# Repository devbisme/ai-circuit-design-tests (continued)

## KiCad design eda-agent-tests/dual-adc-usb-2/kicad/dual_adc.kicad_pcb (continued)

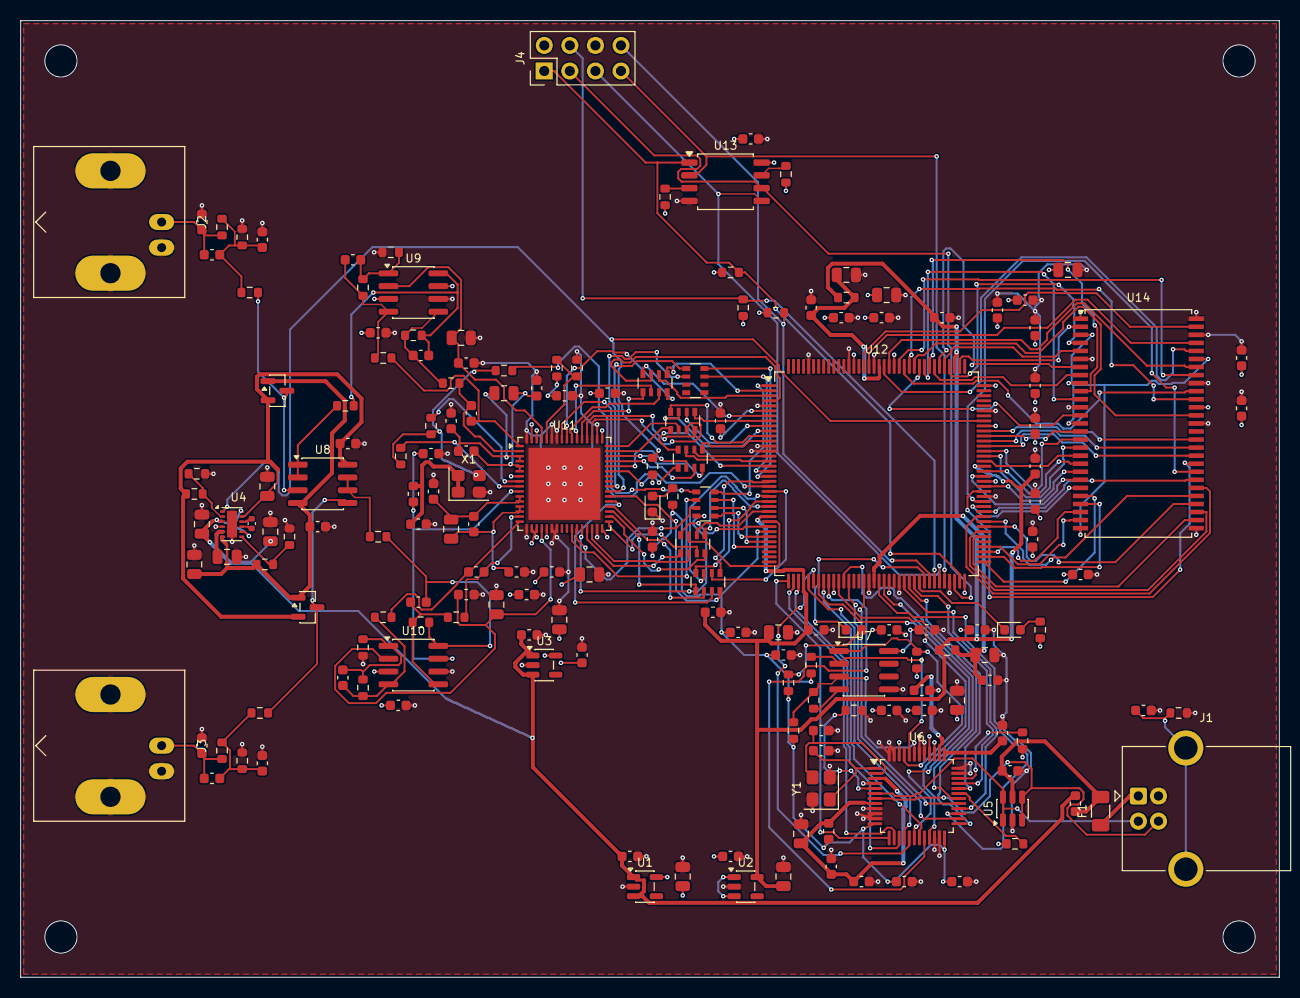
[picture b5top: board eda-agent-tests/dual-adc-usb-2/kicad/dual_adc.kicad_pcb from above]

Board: 4 copper layers, 125.0 x 95.0 mm, 179 parts (0 on the bottom side), 185 nets.

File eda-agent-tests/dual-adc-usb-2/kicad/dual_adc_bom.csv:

"Refs","Value","Footprint","MPN","Manufacturer","Tolerance","Qty"
"C1,C11,C18,C25","4.7uF","Capacitor_SMD:C_0805_2012Metric","","","","4"
"C2,C4,C6,C7,C49,C50,C54,C55","1uF","Capacitor_SMD:C_0603_1608Metric","","","","8"
"C3,C5,C8,C61,C69,C80,C81,C83,C93","10uF","Capacitor_SMD:C_0805_2012Metric","","","","9"
"C9,C12,C13,C48,C51,C53,C56","2.2uF","Capacitor_SMD:C_0805_2012Metric","","","","7"
"C10","1uF","Capacitor_SMD:C_0402_1005Metric","","","","1"
"C14","4.7nF","Capacitor_SMD:C_0603_1608Metric","","","","1"
"C15,C19-C24,C26-C30,C36,C37,C44,C45,C47,C52,C57-C60,C62-C68,C70-C79,C82,C84-C92","100nF","Capacitor_SMD:C_0603_1608Metric","","","","49"
"C16,C17","27pF","Capacitor_SMD:C_0603_1608Metric","","","","2"
"C31,C39","12pF","Capacitor_SMD:C_0603_1608Metric","","","","2"
"C32,C40","2.7pF","Capacitor_SMD:C_0603_1608Metric","","","","2"
"C33,C41","22pF","Capacitor_SMD:C_0603_1608Metric","","","","2"
"C34,C35,C42,C43","33pF","Capacitor_SMD:C_0603_1608Metric","","","","4"
"C38,C46","100pF","Capacitor_SMD:C_0603_1608Metric","","","","2"
"D1","Green","LED_SMD:LED_0603_1608Metric","","","","1"
"D2,D3","BAV99","Package_TO_SOT_SMD:SOT-23","BAV99,215","Nexperia","","2"
"D4,D5","Yellow","LED_SMD:LED_0603_1608Metric","","","","2"
"F1","750mA","Fuse:Fuse_1206_3216Metric","0ZCJ0050AF2E","Bel Fuse","","1"
"FB1","120R@100MHz 2A","Inductor_SMD:L_0603_1608Metric","BLM18AG601SN1D","Murata","","1"
"FB2,FB3","600R@100MHz","Inductor_SMD:L_0603_1608Metric","BLM18AG601SN1D","Murata","","2"
"J1","USB_B","Connector_USB:USB_B_OST_USB-B1HSxx_Horizontal","USB-B1HSW6","On Shore Technology","","1"
"J2","BNC_A","Connector_Coaxial:BNC_Amphenol_B6252HB-NPP3G-50_Horizontal","B6252HB-NPP3G-50","Amphenol RF","","1"
"J3","BNC_B","Connector_Coaxial:BNC_Amphenol_B6252HB-NPP3G-50_Horizontal","B6252HB-NPP3G-50","Amphenol RF","","1"
"J4","PROG","Connector_PinHeader_2.54mm:PinHeader_2x04_P2.54mm_Vertical","","","","1"
"R1,R9,R10,R12-R14,R33,R40-R44","10k","Resistor_SMD:R_0603_1608Metric","","","","12"
"R2","232k","Resistor_SMD:R_0603_1608Metric","","","","1"
"R3,R5","100k","Resistor_SMD:R_0603_1608Metric","","","","2"
"R4","226k","Resistor_SMD:R_0603_1608Metric","","","","1"
"R6,R17-R21,R26-R30,R45,R46","1k","Resistor_SMD:R_0603_1608Metric","","","","13"
"R7","1M","Resistor_SMD:R_0603_1608Metric","","","","1"
"R8","12k","Resistor_SMD:R_0603_1608Metric","","","1%","1"
"R11","2.2k","Resistor_SMD:R_0603_1608Metric","","","","1"
"R15,R24","909k","Resistor_SMD:R_0603_1608Metric","","","0.1%","2"
"R16,R25","90.9k","Resistor_SMD:R_0603_1608Metric","","","0.1%","2"
"R22,R23,R31,R32","49.9","Resistor_SMD:R_0603_1608Metric","","","","4"
"R34","20k","Resistor_SMD:R_0603_1608Metric","","","","1"
"R35-R37","33","Resistor_SMD:R_0603_1608Metric","","","","3"
"R38,R39","100","Resistor_SMD:R_0603_1608Metric","","","","2"
"RN1-RN7","33","Resistor_SMD:R_Array_Convex_4x0603","CAY16-330J4LF","Bourns","","7"
"U1","AP2112K-3.3","Package_TO_SOT_SMD:SOT-23-5","AP2112K-3.3TRG1","Diodes Inc","","1"
"U2","AP2112K-1.2","Package_TO_SOT_SMD:SOT-23-5","AP2112K-1.2TRG1","Diodes Inc","","1"
"U3","LP5907MFX-3.3","Package_TO_SOT_SMD:SOT-23-5","LP5907MFX-3.3/NOPB","Texas Instruments","","1"
"U4","LM27762","Package_SON:WSON-12-1EP_3x2mm_P0.5mm_EP1x2.65","LM27762DSSR","Texas Instruments","","1"
"U5","USBLC6-2SC6","Package_TO_SOT_SMD:SOT-23-6","USBLC6-2SC6","STMicroelectronics","","1"
"U6","FT232HL","Package_QFP:LQFP-48_7x7mm_P0.5mm","FT232HL-REEL","FTDI","","1"
"U7","93LC56B","Package_SO:SOIC-8_3.9x4.9mm_P1.27mm","93LC56BT-I/SN","Microchip","","1"
"U8","OPA1656ID","Package_SO:SOIC-8_3.9x4.9mm_P1.27mm","OPA1656IDR","Texas Instruments","","1"
"U9,U10","THS4521ID","Package_SO:SOIC-8_3.9x4.9mm_P1.27mm","THS4521IDR","Texas Instruments","","2"
"U11","LTC2290CUP","Package_DFN_QFN:QFN-64-1EP_9x9mm_P0.5mm_EP7.15x7.15mm","LTC2290CUP#PBF","Analog Devices","","1"
"U12","ICE40HX4K-TQ144","Package_QFP:TQFP-144_20x20mm_P0.5mm","ICE40HX4K-TQ144","Lattice","","1"
"U13","W25Q32JVSS","Package_SO:SOIC-8_5.3x5.3mm_P1.27mm","W25Q32JVSSIQ","Winbond","","1"
"U14","MT48LC16M16A2TG-6A","Package_SO:TSOP-II-54_22.2x10.16mm_P0.8mm","MT48LC16M16A2P-6A:G","Micron","","1"
"X1","ASE-10.000MHz","Oscillator:Oscillator_SMD_Abracon_ASE-4Pin_3.2x2.5mm","ASE-10.000MHZ-LC-T","Abracon","","1"
"Y1","12MHz","Crystal:Crystal_SMD_3225-4Pin_3.2x2.5mm","ABM8-12.000MHZ-B2-T","Abracon","","1"

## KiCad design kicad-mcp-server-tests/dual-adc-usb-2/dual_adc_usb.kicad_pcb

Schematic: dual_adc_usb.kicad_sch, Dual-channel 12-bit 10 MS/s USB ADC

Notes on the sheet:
Power: USB-C input, regulators
Analog front ends (A, B)
ADC and sample clock
FPGA, SDRAM, config flash
USB 2.0 interface (FT2232H)
DUAL-CHANNEL 12-BIT 10 MS/s USB ADC (see DESIGN.md for options and rationale) Signal path (per channel): BNC -> 1 Mohm || ~19 pF input, compensated /10.06 divider (2 x 453k + 100k) -> BAV99 clamp to +/-3.3 V -> OPA810 FET-input unity buffer -> THS4521 FDA (G = 1, VOCM = ADC VCM 1.5 V) -> 49.9R/33pF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

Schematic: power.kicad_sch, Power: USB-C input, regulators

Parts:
C1: 4.7nF 100V; C_0603_1608Metric
C2: 4.7uF; C_0805_2012Metric
C3: 22uF; C_0805_2012Metric
C4: 100nF; C_0603_1608Metric
C5, C6, C7, C8, C9, C10, C11: 1uF; C_0603_1608Metric
C12, C13: 2.2uF; C_0603_1608Metric
D1: green; LED_0603_1608Metric
F1: 0.75A hold; Fuse_1206_3216Metric
H1, H2, H3, H4: M3; MountingHole_3.2mm_M3
J1: USB-C (USB 2.0); USB_C_Receptacle_GCT_USB4105-xx-A_16P_TopMnt_Horizontal
L1: 2.2uH 1.5A; L_Taiyo-Yuden_NR-30xx
R1, R2: 5.1k; R_0603_1608Metric
R3: 1M; R_0603_1608Metric
R4: 169k 1%; R_0603_1608Metric
R5: 100k 1%; R_0603_1608Metric
R6: 1k; R_0603_1608Metric
U1: USBLC6-2SC6; SOT-23-6
U2: TPS62162DSGR; WSON-8-1EP_2x2mm_P0.5mm_EP0.9x1.6mm_ThermalVias
U3: AP2112K-1.2; SOT-23-5
U4: LP5907MFX-3.3; SOT-23-5
U5: LP5907MFX-3.0; SOT-23-5
U6: LM27761DSGR; WSON-8-1EP_2x2mm_P0.5mm_EP0.9x1.6mm

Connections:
+1V2: C6.1, U3.5 (VOUT); also elsewhere on the board
+3V0A: C10.1, U5.5 (OUT); also elsewhere on the board
+3V3: C3.1, C4.1, C5.1, L1.2, R6.1, U2.6 (VOS), U3.1 (VIN), U3.3 (EN); also elsewhere on the board
+3V3A: C8.1, U4.5 (OUT); also elsewhere on the board
+5V: C2.1, C7.1, C9.1, F1.2, U2.2 (VIN), U2.3 (EN), U4.1 (IN), U4.3 (EN), U5.1 (IN), U5.3 (EN), U6.1 (VIN), U6.6 (EN)
-3V3A: C13.1, R4.1, U6.4 (VOUT); also elsewhere on the board
CC1: J1.A5 (CC1), R1.1
CC2: J1.B5 (CC2), R2.1
CPOUT: C12.1, U6.3 (CPOUT)
CP_N: C11.2, U6.7 (C-)
CP_P: C11.1, U6.8 (C+)
GND: C1.2, C2.2, C3.2, C4.2, C5.2, C6.2, C7.2, C8.2, C9.2, C10.2, C12.2, C13.2, D1.1 (K), J1.A1 (GND), J1.A12 (GND), J1.B1 (GND), J1.B12 (GND), R1.2, R2.2, R3.2, R5.2, U1.2 (GND), U2.1 (PGND), U2.4 (AGND), U2.5 (FB), U2.9 (PAD), U3.2 (GND), U4.2 (GND), U5.2 (GND), U6.2 (GND), U6.9 (PAD); also elsewhere on the board
LED_PWR: D1.2 (A), R6.2
NFB: R4.2, R5.1, U6.5 (VFB)
SHIELD: C1.1, J1.S1 (SHIELD), R3.1
SW_3V3: L1.1, U2.7 (SW)
USB_DM: J1.A7 (D-), J1.B7 (D-), U1.3 (I/O2), U1.4 (I/O2); also elsewhere on the board
USB_DP: J1.A6 (D+), J1.B6 (D+), U1.1 (I/O1), U1.6 (I/O1); also elsewhere on the board
VBUS: F1.1, J1.A4 (VBUS), J1.A9 (VBUS), J1.B4 (VBUS), J1.B9 (VBUS), U1.5 (VBUS)

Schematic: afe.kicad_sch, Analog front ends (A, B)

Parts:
C101, C201: 15pF C0G 100V; C_0805_2012Metric
C102, C202: 4.7pF C0G 100V; C_0805_2012Metric
C103, C203: 30pF C0G; C_0603_1608Metric
C104, C204: 4.5-20pF; C_Trimmer_Murata_TZC3
C105, C106, C110, C205, C206, C210: 100nF; C_0603_1608Metric
C107, C108, C207, C208: 22pF C0G; C_0603_1608Metric
C109, C209: 33pF C0G; C_0603_1608Metric
D101, D201: BAV99; SOT-23
J101: BNC IN_A; BNC_Amphenol_B6252HB-NPP3G-50_Horizontal
J201: BNC IN_B; BNC_Amphenol_B6252HB-NPP3G-50_Horizontal
R101, R102, R201, R202: 453k 0.1%; R_0805_2012Metric
R103, R203: 100k 0.1%; R_0603_1608Metric
R104, R204: 1k; R_0603_1608Metric
R105, R106, R107, R108, R205, R206, R207, R208: 1.00k 0.1%; R_0603_1608Metric
R109, R110, R209, R210: 49.9; R_0603_1608Metric
U101, U201: OPA810IDBVR; SOT-23-5
U102, U202: THS4521IDGK; VSSOP-8_3x3mm_P0.65mm

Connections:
+3V3A: C105.1, C110.1, C205.1, C210.1, D101.2 (A), D201.2 (A), U101.5 (V+), U102.3 (V_{S+}), U102.7 (~PD), U201.5 (V+), U202.3 (V_{S+}), U202.7 (~PD); also elsewhere on the board
-3V3A: C106.1, C206.1, D101.1 (K), D201.1 (K), U101.2 (V-), U201.2 (V-); also elsewhere on the board
AIN_N_A: C109.2, R110.2; also elsewhere on the board
AIN_N_B: C209.2, R210.2; also elsewhere on the board
AIN_P_A: C109.1, R109.2; also elsewhere on the board
AIN_P_B: C209.1, R209.2; also elsewhere on the board
ATT_A: C102.2, C103.1, C104.1, D101.3 (K), R102.2, R103.1, R104.1
ATT_B: C202.2, C203.1, C204.1, D201.3 (K), R202.2, R203.1, R204.1
ATT_M_A: R101.2, R102.1
ATT_M_B: R201.2, R202.1
BUFIN_A: R104.2, U101.3 (+)
BUFIN_B: R204.2, U201.3 (+)
BUF_A: R105.1, U101.1, U101.4 (-)
BUF_B: R205.1, U201.1, U201.4 (-)
FDA_N_A: C108.2, R106.2, R108.2, U102.1 (-)
FDA_N_B: C208.2, R206.2, R208.2, U202.1 (-)
FDA_P_A: C107.2, R105.2, R107.2, U102.8 (+)
FDA_P_B: C207.2, R205.2, R207.2, U202.8 (+)
FOUT_N_A: C107.1, R107.1, R110.1, U102.5
FOUT_N_B: C207.1, R207.1, R210.1, U202.5
FOUT_P_A: C108.1, R108.1, R109.1, U102.4
FOUT_P_B: C208.1, R208.1, R209.1, U202.4
GND: C101.2, C103.2, C104.2, C105.2, C106.2, C110.2, C201.2, C203.2, C204.2, C205.2, C206.2, C210.2, J101.2 (Ext), J201.2 (Ext), R103.2, R106.1, R203.2, R206.1, U102.6 (V_{S-}), U202.6 (V_{S-}); also elsewhere on the board
IN_A: C101.1, C102.1, J101.1 (In), R101.1
IN_B: C201.1, C202.1, J201.1 (In), R201.1
VCM_A: U102.2 (V_{OCM}); also elsewhere on the board
VCM_B: U202.2 (V_{OCM}); also elsewhere on the board

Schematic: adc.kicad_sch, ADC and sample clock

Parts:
C301, C302, C303, C304, C306, C307, C309, C313, C318: 100nF; C_0603_1608Metric
C305: 10uF; C_0805_2012Metric
C308, C312, C316, C317: 2.2uF; C_0603_1608Metric
C310, C311, C314, C315, C319: 1uF; C_0603_1608Metric
FB301: 600R@100MHz; L_0603_1608Metric
R301: 10k; R_0603_1608Metric
R302: 20k; R_0603_1608Metric
R303, R304, R305: 33; R_0603_1608Metric
RN301, RN302, RN303, RN304, RN305, RN306, RN307: 4x33; R_Array_Convex_4x0603
U301: LTC2290CUP; QFN-64-1EP_9x9mm_P0.5mm_EP7.15x7.15mm
Y301: ASE-10.000MHZ-LC-T; Oscillator_SMD_Abracon_ASE-4Pin_3.2x2.5mm

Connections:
+3V0A: C301.1, C302.1, C303.1, C304.1, C305.1, FB301.1, R301.1, U301.7 (VDD), U301.10 (VDD), U301.18 (VDD), U301.19 (SENSEB), U301.21 (MUX), U301.62 (SENSEA), U301.63 (VDD); also elsewhere on the board
+3V3: C306.1, C307.1, U301.32 (OVDD), U301.49 (OVDD); also elsewhere on the board
ADC_MODE: R301.2, R302.1, U301.60 (MODE)
AIN_N_A: U301.2 (AINA-); also elsewhere on the board
AIN_N_B: U301.15 (AINB-); also elsewhere on the board
AIN_P_A: U301.1 (AINA+); also elsewhere on the board
AIN_P_B: U301.16 (AINB+); also elsewhere on the board
CLK10M: R305.2; also elsewhere on the board
CLK_ADC_A: R303.2, U301.8 (CLKA)
CLK_ADC_B: R304.2, U301.9 (CLKB)
DA0: RN301.8 (R1.2); also elsewhere on the board
DA0_S: RN301.1 (R1.1), U301.43 (DA0)
DA1: RN301.7 (R2.2); also elsewhere on the board
DA1_S: RN301.2 (R2.1), U301.44 (DA1)
DA2: RN301.6 (R3.2); also elsewhere on the board
DA2_S: RN301.3 (R3.1), U301.45 (DA2)
DA3: RN301.5 (R4.2); also elsewhere on the board
DA3_S: RN301.4 (R4.1), U301.46 (DA3)
DA4: RN302.8 (R1.2); also elsewhere on the board
DA4_S: RN302.1 (R1.1), U301.47 (DA4)
DA5: RN302.7 (R2.2); also elsewhere on the board
DA5_S: RN302.2 (R2.1), U301.48 (DA5)
DA6: RN302.6 (R3.2); also elsewhere on the board
DA6_S: RN302.3 (R3.1), U301.51 (DA6)
DA7: RN302.5 (R4.2); also elsewhere on the board
DA7_S: RN302.4 (R4.1), U301.52 (DA7)
DA8: RN303.8 (R1.2); also elsewhere on the board
DA8_S: RN303.1 (R1.1), U301.53 (DA8)
DA9: RN303.7 (R2.2); also elsewhere on the board
DA9_S: RN303.2 (R2.1), U301.54 (DA9)
DA10: RN303.6 (R3.2); also elsewhere on the board
DA10_S: RN303.3 (R3.1), U301.55 (DA10)
DA11: RN303.5 (R4.2); also elsewhere on the board
DA11_S: RN303.4 (R4.1), U301.56 (DA11)
DB0: RN304.7 (R2.2); also elsewhere on the board
DB0_S: RN304.2 (R2.1), U301.26 (DB0)
DB1: RN304.6 (R3.2); also elsewhere on the board
DB1_S: RN304.3 (R3.1), U301.27 (DB1)
DB2: RN304.5 (R4.2); also elsewhere on the board
DB2_S: RN304.4 (R4.1), U301.28 (DB2)
DB3: RN305.8 (R1.2); also elsewhere on the board
DB3_S: RN305.1 (R1.1), U301.29 (DB3)
DB4: RN305.7 (R2.2); also elsewhere on the board
DB4_S: RN305.2 (R2.1), U301.30 (DB4)
DB5: RN305.6 (R3.2); also elsewhere on the board
DB5_S: RN305.3 (R3.1), U301.33 (DB5)
DB6: RN305.5 (R4.2); also elsewhere on the board
DB6_S: RN305.4 (R4.1), U301.34 (DB6)
DB7: RN306.8 (R1.2); also elsewhere on the board
DB7_S: RN306.1 (R1.1), U301.35 (DB7)
DB8: RN306.7 (R2.2); also elsewhere on the board
DB8_S: RN306.2 (R2.1), U301.36 (DB8)
DB9: RN306.6 (R3.2); also elsewhere on the board
DB9_S: RN306.3 (R3.1), U301.37 (DB9)
DB10: RN306.5 (R4.2); also elsewhere on the board
DB10_S: RN306.4 (R4.1), U301.38 (DB10)
DB11: RN307.8 (R1.2); also elsewhere on the board
DB11_S: RN307.1 (R1.1), U301.39 (DB11)
GND: C301.2, C302.2, C303.2, C304.2, C305.2, C306.2, C307.2, C310.2, C311.2, C314.2, C315.2, C316.2, C317.2, C318.2, C319.2, R302.2, U301.17 (GND), U301.22 (SHDNB), U301.23 (~OEB), U301.31 (OGND), U301.50 (OGND), U301.58 (~OEA), U301.59 (SHDNA), U301.64 (GND), U301.65 (GND), Y301.2 (GND); also elsewhere on the board
OFA: RN304.8 (R1.2); also elsewhere on the board
OFA_S: RN304.1 (R1.1), U301.57 (OFA)
OFB: RN307.7 (R2.2); also elsewhere on the board
OFB_S: RN307.2 (R2.1), U301.40 (OFB)
OSC_OUT: R303.1, R304.1, R305.1, Y301.3 (OUT)
OSC_VDD: C318.1, C319.1, FB301.2, Y301.1 (EN), Y301.4 (Vdd)
REFH_A: C308.1, C309.1, C310.1, U301.3 (REFHA), U301.4 (REFHA)
REFH_B: C312.1, C313.1, C314.1, U301.13 (REFHB), U301.14 (REFHB)
REFL_A: C308.2, C309.2, C311.1, U301.5 (REFLA), U301.6 (REFLA)
REFL_B: C312.2, C313.2, C315.1, U301.11 (REFLB), U301.12 (REFLB)
VCM_A: C316.1, U301.61 (VCMA); also elsewhere on the board
VCM_B: C317.1, U301.20 (VCMB); also elsewhere on the board

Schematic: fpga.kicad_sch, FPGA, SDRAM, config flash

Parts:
C401, C403, C409, C418, C428: 10uF; C_0805_2012Metric
C402, C404, C405, C406, C407, C408, C410, C411, C412, C413, C414, C415, C416, C417, C419, C420, C421, C422, C423, C424, C425, C426, C427: 100nF; C_0603_1608Metric
D401: green; LED_0603_1608Metric
D402: yellow; LED_0603_1608Metric
J401: GPIO / trigger; PinHeader_1x08_P2.54mm_Vertical
R401, R402: 100; R_0603_1608Metric
R403, R404, R405, R406, R407: 10k; R_0603_1608Metric
R408: 22; R_0603_1608Metric
R409, R410: 1k; R_0603_1608Metric
U401: ICE40HX4K-TQ144; TQFP-144_20x20mm_P0.5mm
U402: MT48LC16M16A2TG-6A; TSOP-II-54_22.2x10.16mm_P0.8mm
U403: W25Q32JVSSIQ; SOIC-8_5.3x5.3mm_P1.27mm

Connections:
+1V2: C405.1, C406.1, C407.1, C408.1, C409.1, R401.1, R402.1, U401.27 (VCC), U401.40 (VCC), U401.92 (VCC), U401.111 (VCC); also elsewhere on the board
+3V3: C410.1, C411.1, C412.1, C413.1, C414.1, C415.1, C416.1, C417.1, C418.1, C419.1, C420.1, C421.1, C422.1, C423.1, C424.1, C425.1, C426.1, C427.1, C428.1, J401.1, R403.1, R404.1, R405.1, R406.1, R407.1, U401.6 (VCCIO_3), U401.30 (VCCIO_3), U401.46 (VCCIO_2), U401.57 (VCCIO_2), U401.72 (VCC_SPI), U401.89 (VCCIO_1), U401.100 (VCCIO_1), U401.108 (VPP_2V5), U401.123 (VCCIO_0), U401.131 (VCCIO_0), U402.1 (VDD), U402.3 (VDDQ), U402.9 (VDDQ), U402.14 (VDD), U402.27 (VDD), U402.43 (VDDQ), U402.49 (VDDQ), U403.8 (VCC); also elsewhere on the board
CLK10M: U401.49 (IOB_81_GBIN5); also elsewhere on the board
DA0: U401.1 (IOL_2A); also elsewhere on the board
DA1: U401.2 (IOL_2B); also elsewhere on the board
DA2: U401.3 (IOL_3A); also elsewhere on the board
DA3: U401.4 (IOL_3B); also elsewhere on the board
DA4: U401.7 (IOL_4A); also elsewhere on the board
DA5: U401.8 (IOL_4B); also elsewhere on the board
DA6: U401.9 (IOL_5A); also elsewhere on the board
DA7: U401.10 (IOL_5B); also elsewhere on the board
DA8: U401.11 (IOL_8A); also elsewhere on the board
DA9: U401.12 (IOL_8B); also elsewhere on the board
DA10: U401.15 (IOL_10A); also elsewhere on the board
DA11: U401.16 (IOL_10B); also elsewhere on the board
DB0: U401.18 (IOL_12B); also elsewhere on the board
DB1: U401.19 (IOL_13A); also elsewhere on the board
DB2: U401.20 (IOL_13B_GBIN7); also elsewhere on the board
DB3: U401.21 (IOL_14A_GBIN6); also elsewhere on the board
DB4: U401.22 (IOL_14B); also elsewhere on the board
DB5: U401.23 (IOL_17A); also elsewhere on the board
DB6: U401.24 (IOL_17B); also elsewhere on the board
DB7: U401.25 (IOL_18A); also elsewhere on the board
DB8: U401.26 (IOL_18B); also elsewhere on the board
DB9: U401.28 (IOL_23A); also elsewhere on the board
DB10: U401.29 (IOL_23B); also elsewhere on the board
DB11: U401.31 (IOL_24A); also elsewhere on the board
FLASH_CSn: R405.2, U401.71 (IOB_108_SS), U403.1 (~CS); also elsewhere on the board
FLASH_HOLDn: R407.2, U403.7 (~HOLD/~RESET/IO_{3})
FLASH_MISO: U401.68 (IOB_106_SDI), U403.2 (DO/IO_{1}); also elsewhere on the board
FLASH_MOSI: U401.67 (IOB_105_SDO), U403.5 (DI/IO_{0}); also elsewhere on the board
FLASH_SCK: U401.70 (IOB_107_SCK), U403.6 (CLK); also elsewhere on the board
FLASH_WPn: R406.2, U403.3 (~WP/IO_{2})
FPGA_CDONE: R404.2, U401.65 (CDONE); also elsewhere on the board
FPGA_CRESETn: R403.2, U401.66 (~CRESET); also elsewhere on the board
FT_CLKOUT: U401.93 (IOR_140_GBIN3); also elsewhere on the board
FT_D0: U401.87 (IOR_136); also elsewhere on the board
FT_D1: U401.88 (IOR_137); also elsewhere on the board
FT_D2: U401.90 (IOR_138); also elsewhere on the board
FT_D3: U401.91 (IOR_139); also elsewhere on the board
FT_D4: U401.94 (IOR_141_GBIN2); also elsewhere on the board
FT_D5: U401.95 (IOR_144); also elsewhere on the board
FT_D6: U401.96 (IOR_146); also elsewhere on the board
FT_D7: U401.97 (IOR_147); also elsewhere on the board
FT_OEn: U401.104 (IOR_164); also elsewhere on the board
FT_RDn: U401.101 (IOR_160); also elsewhere on the board
FT_RXFn: U401.98 (IOR_148); also elsewhere on the board
FT_SIWU: U401.105 (IOR_165); also elsewhere on the board
FT_TXEn: U401.99 (IOR_152); also elsewhere on the board
FT_WRn: U401.102 (IOR_161); also elsewhere on the board
GND: C401.2, C402.2, C403.2, C404.2, C405.2, C406.2, C407.2, C408.2, C409.2, C410.2, C411.2, C412.2, C413.2, C414.2, C415.2, C416.2, C417.2, C418.2, C419.2, C420.2, C421.2, C422.2, C423.2, C424.2, C425.2, C426.2, C427.2, C428.2, D401.1 (K), D402.1 (K), J401.8, U401.5 (GND), U401.13 (GND), U401.14 (GND), U401.53 (GNDPLL0), U401.59 (GND), U401.69 (GND), U401.86 (GND), U401.103 (GND), U401.127 (GNDPLL1), U401.132 (GND), U401.140 (GND), U402.6 (VSSQ), U402.12 (VSSQ), U402.28 (VSS), U402.41 (VSS), U402.46 (VSSQ), U402.52 (VSSQ), U402.54 (VSS), U403.4 (GND); also elsewhere on the board
GPIO0: J401.2, U401.37 (IOB_56)
GPIO1: J401.3, U401.38 (IOB_57)
GPIO2: J401.4, U401.39 (IOB_61)
GPIO3: J401.5, U401.41 (IOB_63)
GPIO4: J401.6, U401.42 (IOB_64)
GPIO5: J401.7, U401.43 (IOB_71)
LED1: R409.1, U401.106 (IOR_166)
LED1_A: D401.2 (A), R409.2
LED2: R410.1, U401.107 (IOR_167)
LED2_A: D402.2 (A), R410.2
OFA: U401.17 (IOL_12A); also elsewhere on the board
OFB: U401.32 (IOL_24B); also elsewhere on the board
SD_A0: U401.130 (IOT_206), U402.23 (A0)
SD_A1: U401.134 (IOT_212), U402.24 (A1)
SD_A2: U401.135 (IOT_213), U402.25 (A2)
SD_A3: U401.136 (IOT_214), U402.26 (A3)
SD_A4: U401.137 (IOT_215), U402.29 (A4)
SD_A5: U401.138 (IOT_216), U402.30 (A5)
SD_A6: U401.139 (IOT_217), U402.31 (A6)
SD_A7: U401.141 (IOT_219), U402.32 (A7)
SD_A8: U401.142 (IOT_220), U402.33 (A8)
SD_A9: U401.143 (IOT_221), U402.34 (A9)
SD_A10: U401.144 (IOT_222), U402.22 (A10)
SD_A11: U401.73 (IOR_109), U402.35 (A11)
SD_A12: U401.74 (IOR_110), U402.36 (A12)
SD_BA0: U401.75 (IOR_111), U402.20 (BA0)
SD_BA1: U401.76 (IOR_112), U402.21 (BA1)
SD_CASn: U401.82 (IOR_118), U402.17 (~CAS)
SD_CKE: U401.84 (IOR_120), U402.37 (CKE)
SD_CLK: R408.2, U402.38 (CLK)
SD_CLK_FPGA: R408.1, U401.85 (IOR_128)
SD_CSn: U401.80 (IOR_116), U402.19 (~CS)
SD_DQ0: U401.110 (IOT_168), U402.2 (DQ0)
SD_DQ1: U401.112 (IOT_169), U402.4 (DQ1)
SD_DQ2: U401.113 (IOT_170), U402.5 (DQ2)
SD_DQ3: U401.114 (IOT_171), U402.7 (DQ3)
SD_DQ4: U401.115 (IOT_172), U402.8 (DQ4)
SD_DQ5: U401.116 (IOT_173), U402.10 (DQ5)
SD_DQ6: U401.117 (IOT_174), U402.11 (DQ6)
SD_DQ7: U401.118 (IOT_177), U402.13 (DQ7)
SD_DQ8: U401.119 (IOT_178), U402.42 (DQ8)
SD_DQ9: U401.120 (IOT_179), U402.44 (DQ9)
SD_DQ10: U401.121 (IOT_181), U402.45 (DQ10)
SD_DQ11: U401.122 (IOT_190), U402.47 (DQ11)
SD_DQ12: U401.124 (IOT_191), U402.48 (DQ12)
SD_DQ13: U401.125 (IOT_192), U402.50 (DQ13)
SD_DQ14: U401.128 (IOT_197_GBIN1), U402.51 (DQ14)
SD_DQ15: U401.129 (IOT_198_GBIN0), U402.53 (DQ15)
SD_DQMH: U401.79 (IOR_115), U402.39 (DQMH)
SD_DQML: U401.78 (IOR_114), U402.15 (DQML)
SD_RASn: U401.81 (IOR_117), U402.18 (~RAS)
SD_WEn: U401.83 (IOR_119), U402.16 (~WE)
VCCPLL0: C401.1, C402.1, R401.2, U401.54 (VCCPLL0)
VCCPLL1: C403.1, C404.1, R402.2, U401.126 (VCCPLL1)

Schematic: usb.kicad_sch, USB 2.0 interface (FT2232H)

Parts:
C501, C505, C507, C509, C510, C511, C513, C514, C515, C516: 100nF; C_0603_1608Metric
C502, C503: 27pF; C_0603_1608Metric
C504, C506, C508, C512: 4.7uF; C_0603_1608Metric
FB501, FB502: 600R@100MHz; L_0603_1608Metric
R501: 12k 1%; R_0603_1608Metric
R502, R504, R505, R506: 10k; R_0603_1608Metric
R503: 2.2k; R_0603_1608Metric
U501: FT2232HL; LQFP-64_10x10mm_P0.5mm
U502: 93LC56BT-I/SN; SOIC-8_3.9x4.9mm_P1.27mm
Y501: 12MHz; Crystal_SMD_3225-4Pin_3.2x2.5mm

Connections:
+1V8_FT: C508.1, C509.1, C510.1, C511.1, U501.12 (VCORE), U501.37 (VCORE), U501.49 (VREGOUT), U501.64 (VCORE)
+3V3: C501.1, C512.1, C513.1, C514.1, C515.1, C516.1, FB501.1, FB502.1, R502.1, R504.1, R505.1, R506.1, U501.20 (VCCIO), U501.31 (VCCIO), U501.42 (VCCIO), U501.50 (VREGIN), U501.56 (VCCIO), U502.8 (VCC); also elsewhere on the board
EE_CLK: R505.2, U501.62 (EECLK), U502.2 (SCLK)
EE_CS: R504.2, U501.63 (EECS), U502.1 (CS)
EE_DATA: R503.2, R506.2, U501.61 (EEDATA), U502.3 (DI)
EE_DO: R503.1, U502.4 (DO)
FLASH_CSn: U501.43 (BDBUS4); also elsewhere on the board
FLASH_MISO: U501.40 (BDBUS2); also elsewhere on the board
FLASH_MOSI: U501.39 (BDBUS1); also elsewhere on the board
FLASH_SCK: U501.38 (BDBUS0); also elsewhere on the board
FPGA_CDONE: U501.45 (BDBUS6); also elsewhere on the board
FPGA_CRESETn: U501.46 (BDBUS7); also elsewhere on the board
FT_CLKOUT: U501.32 (ACBUS5); also elsewhere on the board
FT_D0: U501.16 (ADBUS0); also elsewhere on the board
FT_D1: U501.17 (ADBUS1); also elsewhere on the board
FT_D2: U501.18 (ADBUS2); also elsewhere on the board
FT_D3: U501.19 (ADBUS3); also elsewhere on the board
FT_D4: U501.21 (ADBUS4); also elsewhere on the board
FT_D5: U501.22 (ADBUS5); also elsewhere on the board
FT_D6: U501.23 (ADBUS6); also elsewhere on the board
FT_D7: U501.24 (ADBUS7); also elsewhere on the board
FT_OEn: U501.33 (ACBUS6); also elsewhere on the board
FT_RDn: U501.28 (ACBUS2); also elsewhere on the board
FT_REF: R501.1, U501.6 (REF)
FT_RESETn: R502.2, U501.14 (~RESET)
FT_RXFn: U501.26 (ACBUS0); also elsewhere on the board
FT_SIWU: U501.30 (ACBUS4); also elsewhere on the board
FT_TXEn: U501.27 (ACBUS1); also elsewhere on the board
FT_WRn: U501.29 (ACBUS3); also elsewhere on the board
GND: C501.2, C502.2, C503.2, C504.2, C505.2, C506.2, C507.2, C508.2, C509.2, C510.2, C511.2, C512.2, C513.2, C514.2, C515.2, C516.2, R501.2, U501.1 (GND), U501.5 (GND), U501.10 (AGND), U501.11 (GND), U501.13 (TEST), U501.15 (GND), U501.25 (GND), U501.35 (GND), U501.47 (GND), U501.51 (GND), U502.5 (GND), Y501.2 (G), Y501.4 (G); also elsewhere on the board
USB_DM: U501.7 (DM); also elsewhere on the board
USB_DP: U501.8 (DP); also elsewhere on the board
VPHY: C504.1, C505.1, FB501.2, U501.4 (VPHY)
VPLL: C506.1, C507.1, FB502.2, U501.9 (VPLL)
XTAL_I: C502.1, U501.2 (OSCI), Y501.1
XTAL_O: C503.1, U501.3 (OSCO), Y501.3

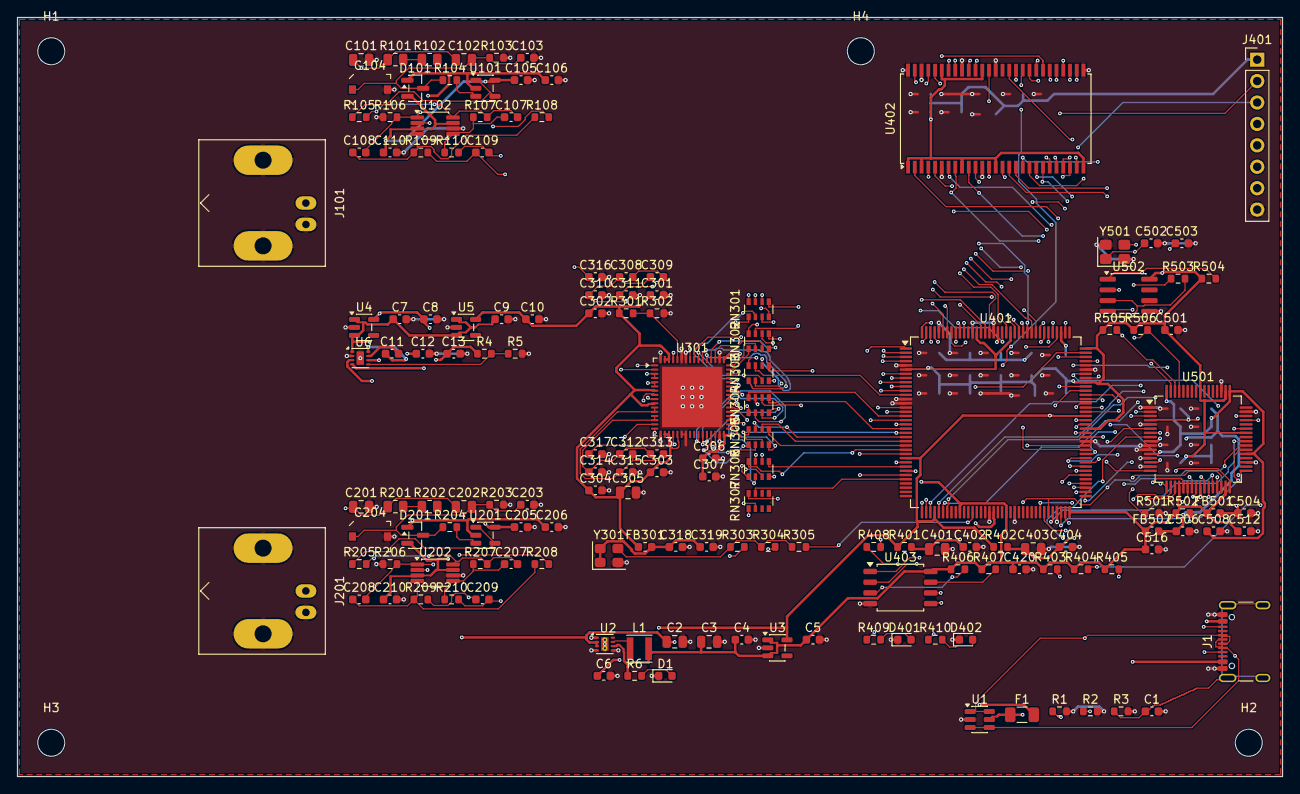
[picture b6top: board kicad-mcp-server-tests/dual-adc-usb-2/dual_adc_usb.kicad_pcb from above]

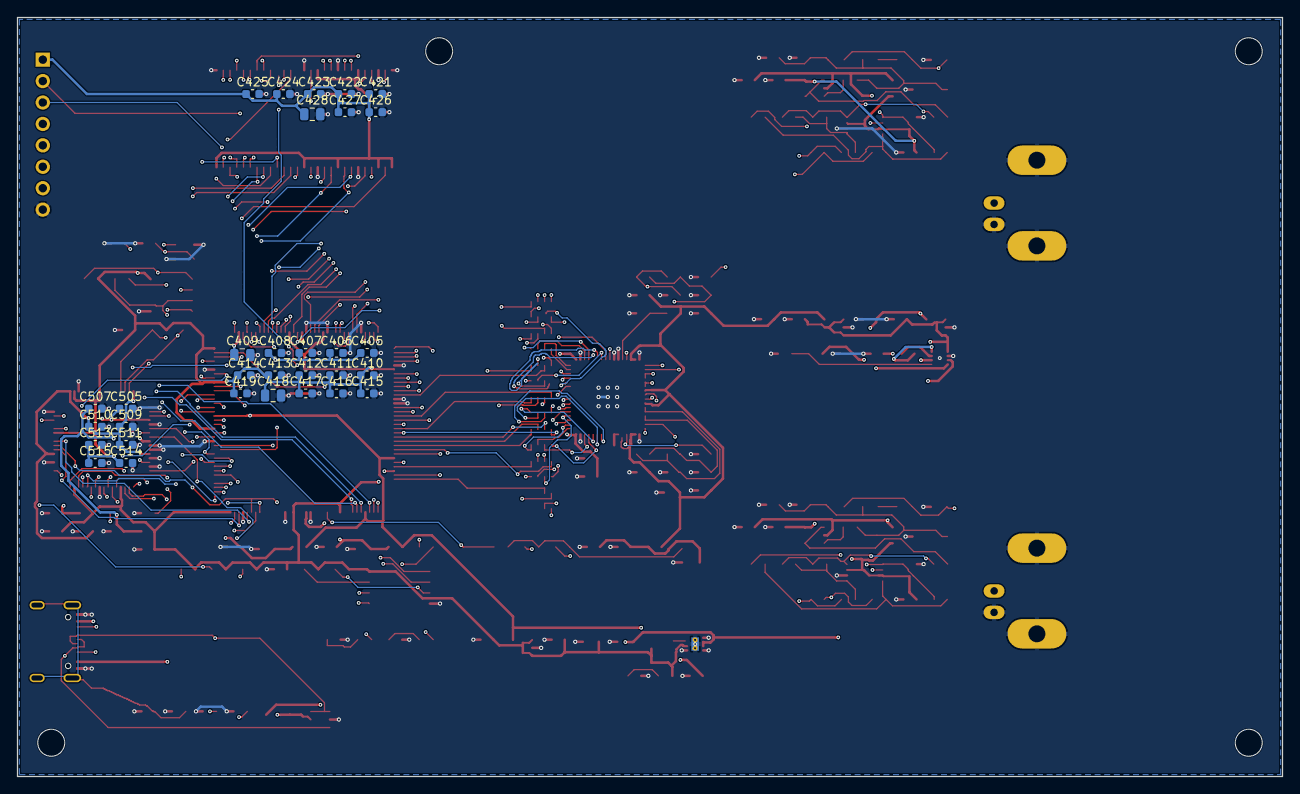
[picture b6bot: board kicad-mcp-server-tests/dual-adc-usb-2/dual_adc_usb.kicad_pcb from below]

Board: 4 copper layers, 150.0 x 90.0 mm, 186 parts (31 on the bottom side), 191 nets.

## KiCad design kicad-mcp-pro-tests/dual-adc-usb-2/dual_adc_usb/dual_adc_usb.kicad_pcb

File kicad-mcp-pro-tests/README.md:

# kicad-mcp-pro — tests

## Tool under test

[kicad-mcp-pro](https://github.com/oaslananka/kicad-mcp-pro) is an MCP server plus a Claude
Code plugin of 7 skills (`kicad-design-review`, `schematic-review`, `pcb-design`,
`drc-check`, `fabrication-output`, `visual-excellence`, `wired-subcircuit-design`). With the
configuration used here, it exposes 289 tools for:

- Inspecting and checking designs: schematic and PCB queries, net tracing, ERC/DRC, DFM,
  quality gates, and SI/PI/EMC/thermal estimates.
- Authoring schematics: symbols, wires, labels, sheets, and `sch_build_circuit`.
- Limited PCB edits.
- Manufacturing exports, and part sourcing (JLCPCB by default; Nexar, DigiKey and Mouser
  need API keys).

ERC, DRC and exports run through `kicad-cli`. Live PCB edits need KiCad open with its IPC
API enabled. Installation is described in [`setup.md`](setup.md).

The tool is a hybrid (both analyzer and generator), so it is tested in both roles, like
[kicad-mcp-server](../kicad-mcp-server-tests/).

- **Version:** kicad-mcp-pro 4.1.0 from PyPI. The plugin skills are from the repo at tag
  `mcp-server-v4.1.0` (commit 7611c20, 2026-10-09).
- **Profile / mode:** `full` / `write` (see [`setup.md`](setup.md)).
- **Model:** Claude Opus 5.5 on a Claude Pro plan, Claude Code v2.1.296 (both runs).
- **Backend:** KiCad 10.0.4 `kicad-cli` (`~/bin/kicad10-root/bin/kicad-cli`), Freerouting
  2.4.1, ngspice.

## Why this tool

- It claims both review and design capabilities, unlike kicad-happy (analysis only).
- It is newer and much larger than the Seeed kicad-mcp-server, which was missing tools for
  sheets, no-connects, netlist import, placement and routing.

## Runs

| Run | What it tests | Prompts | Outcome | Equiv. API cost | Time |
|---|---|---|---|---|---|
| [`dual-adc-usb-1`](dual-adc-usb-1/) | **Analysis** and fab outputs for an existing design | 4, plus 2 for the summary | ERC/DRC 0 errors; quality gate FAIL, mostly false positives; Gerbers, BOM, CPL, PNG | $2.24 | ~16 min wall clock, ~5 min working |
| [`dual-adc-usb-2`](dual-adc-usb-2/) | A **full design**, from requirements to Gerbers | 1, plus 1 for the summary | 7-sheet schematic, routed 4-layer board, ERC and DRC 0 errors | $19.42 | ~1h35m wall clock |

Each run directory has an `executive_summary.md`; start there. Costs are the equivalent
first-party API price of the tokens used (`claude_cost.txt`), not what the Pro subscription
billed. They include the summary-writing prompts, so they are slightly higher than the
figures quoted in the executive summaries ($2.07 and $18.90). I have not yet validated the
findings in either run myself.

### dual-adc-usb-1: analyzer on an existing design

The input is the KiCad project produced by
[Konnect run 2](../konnect-tests/dual-adc-usb-2/): a 4-layer, 140 × 90 mm dual-channel
12-bit, 10 MS/s ADC board with a USB 2.0 interface (LTC2290 ADC, iCE40HX4K FPGA, SDRAM,
FT2232HL). The `.kicad_sch`, `.kicad_pcb`, `.kicad_pro`, `.kicad_dru` and `.kicad_prl` files
are unchanged copies of Konnect's; this run did not modify the design. kicad-happy run 1
and kicad-mcp-server run 1 analyzed the same design, so the three tools' findings can be
compared directly.

Prompts, in sequence in one session (from `claude_transcript.txt`):

```
use kicad-pro to analyze the kicad project in this directory. A KiCad 10
executable is in /home/devb/bin/kicad10.
```
```
output gerber files for jlcpcb.
```
```
generate the BOM and pick-and-place files for JLCPCB
```
```
create a PNG of the PCB showing the front and back traces, footprints, and
silkscreen along with the board edges all on a dark-gray background.
```
```
write an executive_summary.md file explaining what you did and what results were
found for this kicad project.
```
```
add the cost and time row
```

Quick look:

- ERC 0 errors (201 of 203 warnings come from a stale global `sym-lib-table`, a machine
  setup problem). DRC 0 errors, 0 unconnected, 343 warnings.
- Real findings were minor: flash WP/HOLD tied to +3V3 (no quad SPI), footprint library
  drift, silkscreen, BNCs overhanging the edge.
- **The kicad-pro quality gate failed, but most of its blocking items were false
  positives** on inspection. It treats label-connected parts as isolated, measures
  decoupling distance and edge clearance from part centres, and counts KiCad's automatic
  `unconnected-(…)` nets as mismatches. Several DFM checks need the live KiCad connection.
- Gerbers/drill, a JLCPCB zip, BOM and CPL were produced. The MCP pick-and-place export was
  in inches and was redone in mm with `kicad-cli`; the JLCPCB column layout and the PNG
  render were done outside the server.
- Server quirks: it refuses output directories outside the project, lost its active project
  once, and returned ERC/DRC results too large for one response.

### dual-adc-usb-2: full design

The prompt is [`dual-adc-prompt.txt`](dual-adc-usb-2/dual-adc-prompt.txt). It is identical
to the one used for Konnect run 2, kicad-mcp-server run 2 and kicad-happy run 2.

Prompts, in sequence in one session, with no other user intervention:

```
create the design described in dual-adc-prompt.txt.
```
```
create executive_summary.md as was done for previous tests.
```

Quick look:

- **Design:** BNC → 1 MΩ compensated ÷10 divider → BAV99 clamp → OPA810 → THS4521 →
  LTC2290; iCE40HX4K with 8 MB SDRAM; FT2232HL (channel A data FIFO, channel B flash
  programming); USB-B; ~320 mA estimated. Decisions with options are in
  [`design_notes.md`](dual-adc-usb-2/design_notes.md).
- **Schematic:** 7 sheets, 175 parts, 233 nets, ERC 0 errors. Each sheet was captured with
  one `sch_build_circuit` call.
- **PCB:** 115 × 85 mm, 4 layers (In1 GND plane). DRC 0 errors, 0 unconnected, 0 parity
  issues, 18 warnings.
- **How the server was used:** as a **design tool** for project and sheet creation,
  schematic capture, ERC, `pcb_sync_from_schematic`, gates, and exports.
- **Server bugs found:**
  - Can't read KiCad 10 `.kicad_symdir` libraries, so pin lookups fail silently. The needed
    libraries were flattened into `dual_adc_usb/libs/`.
  - Multi-unit parts: only one unit resolves, and 92 FPGA nets were silently dropped.
  - Child sheets get a bad instance path; `#PWR` numbers repeat across sheets; PWR_FLAGs
    are added on every sheet; no no-connect support; `sch_delete_symbol` also deleted a
    neighbouring label.
  - PCB tools are gated off if KiCad IPC isn't up at server start. They were called
    in-process through `scripts/mcp_call.py`.
  - The sync pre-check only looks at the root sheet; footprint IDs lack the library
    nickname; auto-placement scored 1/100; DSN/SES routing requires the KiCad GUI.
- **Gaps filled by Claude's own scripts:** placement, GND fanout, Freerouting DSN/SES, a
  small A* router for the last 4 connections, schematic fix-ups and no-connects (all in
  `scripts/`).
- **Not ready for fab:** part data from the model's memory, not datasheets; 2-pole
  anti-alias filter; USB D+/D− not an impedance-controlled pair; shared analog/digital
  ground; nothing simulated; no MPN/LCSC numbers. The `sch_build_circuit` inputs exist only
  in the transcript, so the schematic rebuild is not fully scripted.

## Layout

```
kicad-mcp-pro-tests/
├── README.md                   <- this file
├── setup.md                    <- how kicad-mcp-pro was installed and configured
├── dual-adc-usb-1/             <- run 1: analysis of the Konnect run-2 design
│   ├── executive_summary.md    <- start here
│   ├── claude_transcript.txt   <- session transcript (/export)
│   ├── claude_cost.txt         <- token usage and equivalent API cost
│   ├── session_cost.py         <- script that produced claude_cost.txt
│   ├── dual_adc_usb.kicad_pro, .kicad_pcb, .kicad_dru, .kicad_prl, .kicad_sch
│   ├── afe_a, afe_b, adc, fpga, usb, power .kicad_sch
│   ├── .kicad-mcp/             <- server state
│   └── mcp_out/                <- outputs of this run
│       ├── erc_report.json, drc_report.json
│       ├── schematic_quality_gate.json, pcb_quality_gate.json, dfm_profile_check.json
│       ├── gerber/, dual_adc_usb_jlcpcb.zip   <- Gerbers/drill, and the JLCPCB upload
│       ├── bom.csv, pos/       <- server BOM and pick-and-place (pos/ has inch and mm)
│       ├── jlcpcb/             <- BOM and CPL in JLCPCB's column layout
│       ├── render/             <- dual_adc_usb_pcb.png and pcb.svg
│       └── pcb_sync.net
└── dual-adc-usb-2/             <- run 2: full design from the dual-ADC prompt
    ├── executive_summary.md    <- start here
    ├── design_notes.md         <- requirements, budgets, decisions with options
    ├── dual-adc-prompt.txt     <- the design prompt
    ├── claude_transcript.txt   <- session transcript (/export)
    ├── claude_cost.txt         <- token usage and equivalent API cost
    ├── session_cost.py         <- script that produced claude_cost.txt
    ├── dual_adc_usb/           <- the KiCad project
    │   ├── dual_adc_usb.kicad_pro, .kicad_pcb, .kicad_prl, .kicad_sch
    │   ├── afe_a, afe_b, adc, fpga, memory, usb, power .kicad_sch
    │   ├── libs/, sym-lib-table <- flattened symbol libraries (symdir workaround)
    │   └── output/             <- Gerbers, drill, BOM, pos, schematic.pdf, render_top.png,
    │                              ERC report, quality-gate and DFM JSON
    ├── routing/                <- Freerouting DSN in/out, SES, and log
    └── scripts/                <- workarounds for server gaps
        ├── mcp_call.py         <- calls kicad-mcp-pro tools in-process (gated PCB tools)
        ├── fixup_sch.py        <- fixes sheet instance paths and duplicate #PWR refs
        ├── prune_pwr_flags.py  <- removes surplus PWR_FLAGs
        ├── add_no_connects.py  <- adds no-connect markers
        ├── place_board.py      <- board outline, layers and floorplan placement
        ├── gnd_fanout.py       <- locked GND vias to the In1 plane
        ├── prep_dsn.py         <- makes the DSN Freerouting-friendly
        ├── import_ses.py       <- imports the routed session, adds GND pours
        ├── finish_routes.py    <- A* router for the last connections
        ├── set_netclasses.py   <- net classes (re-run after any pcbnew save)
        └── silk_cleanup.py     <- hides passive refs on silkscreen
```

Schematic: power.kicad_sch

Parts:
C101, C102, C103: 10u; C_0805_2012Metric
C104, C105, C106, C107: 1u; C_0603_1608Metric
C108, C109: 4.7u; C_0603_1608Metric
C110, C111: 2.2u; C_0603_1608Metric
D101: GRN; LED_0603_1608Metric
R101: 274k; R_0603_1608Metric
R102, R104: 100k; R_0603_1608Metric
R103: 374k; R_0603_1608Metric
R105: 1k; R_0603_1608Metric
U101: TLV75733PDBV; SOT-23-5
U102: TLV75712PDBV; SOT-23-5
U103: LP5907MFX-3.3; SOT-23-5
U104: LM27762DSS; WSON-12-1EP_3x2mm_P0.5mm_EP1x2.65_ThermalVias

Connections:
+1V2: C103.1, U102.5 (OUT); also elsewhere on the board
+3.3VA: C106.1, U103.5 (OUT); also elsewhere on the board
+3V3: C102.1, C104.1, R105.1, U101.5 (OUT), U102.1 (IN), U102.3 (EN); also elsewhere on the board
+4V5A: C110.1, R101.1, U104.11 (OUT+); also elsewhere on the board
+5V: C101.1, C105.1, C109.1, U101.1 (IN), U101.3 (EN), U103.1 (IN), U103.3 (EN), U104.3 (VIN), U104.8 (EN-), U104.12 (EN+); also elsewhere on the board
-4V5A: C111.1, R103.1, U104.6 (OUT-); also elsewhere on the board
/Power/CFLY_N: C107.2, U104.9 (C-)
/Power/CFLY_P: C107.1, U104.10 (C+)
/Power/FBN: R103.2, R104.1, U104.7 (FB-)
/Power/FBP: R101.2, R102.1, U104.2 (FB+)
/Power/LED_PWR: D101.2 (A), R105.2
/Power/VCP: C108.1, U104.5 (CP)
GND: C101.2, C102.2, C103.2, C104.2, C105.2, C106.2, C108.2, C109.2, C110.2, C111.2, D101.1 (K), R102.2, R104.2, U101.2 (GND), U102.2 (GND), U103.2 (GND), U104.4 (GND), U104.13 (PAD); also elsewhere on the board

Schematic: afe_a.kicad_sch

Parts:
C201: 18p C0G; C_0603_1608Metric
C202: 160p C0G; C_0603_1608Metric
C203, C204, C207, C208: 100n; C_0603_1608Metric
C205, C206, C209, C210: 33p C0G; C_0603_1608Metric
D201: BAV99; SOT-23
J201: BNC CH_A; BNC_Amphenol_B6252HB-NPP3G-50_Horizontal
R201: 909k 0.1%; R_0603_1608Metric
R202: 101k 0.1%; R_0603_1608Metric
R203: 1k; R_0603_1608Metric
R204, R205: 1.1k 0.1%; R_0603_1608Metric
R206, R207: 1.0k 0.1%; R_0603_1608Metric
R208, R209: 49.9; R_0603_1608Metric
U201: OPA810IDBV; SOT-23-5
U202: THS4521IDGK; VSSOP-8_3x3mm_P0.65mm

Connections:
+3.3VA: C208.1, U202.3 (V_{S+}), U202.7 (~PD); also elsewhere on the board
+4V5A: C203.1, D201.2 (A), U201.5 (V+); also elsewhere on the board
-4V5A: C204.2, D201.1 (K), U201.2 (V-); also elsewhere on the board
/AFE_A/A_BUF_IN: R203.2, U201.3 (+)
/AFE_A/A_BUF_OUT: R204.1, U201.1, U201.4 (-)
/AFE_A/A_FDA_INN: C206.1, R205.2, R207.1, U202.1 (-)
/AFE_A/A_FDA_INP: C205.1, R204.2, R206.1, U202.8 (+)
/AFE_A/A_IN: C201.1, J201.1 (In), R201.1
/AFE_A/A_OUTN: C205.2, R206.2, R209.1, U202.5
/AFE_A/A_OUTP: C206.2, R207.2, R208.1, U202.4
/AFE_A/A_TAP: C201.2, C202.1, D201.3 (K), R201.2, R202.1, R203.1
AINA_N: C210.1, R209.2; also elsewhere on the board
AINA_P: C209.1, R208.2; also elsewhere on the board
GND: C202.2, C203.2, C204.1, C207.2, C208.2, C209.2, C210.2, J201.2 (Ext), R202.2, R205.1, U202.6 (V_{S-}); also elsewhere on the board
VCMA: C207.1, U202.2 (V_{OCM}); also elsewhere on the board

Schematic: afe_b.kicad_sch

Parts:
C301: 18p C0G; C_0603_1608Metric
C302: 160p C0G; C_0603_1608Metric
C303, C304, C307, C308: 100n; C_0603_1608Metric
C305, C306, C309, C310: 33p C0G; C_0603_1608Metric
D301: BAV99; SOT-23
J301: BNC CH_B; BNC_Amphenol_B6252HB-NPP3G-50_Horizontal
R301: 909k 0.1%; R_0603_1608Metric
R302: 101k 0.1%; R_0603_1608Metric
R303: 1k; R_0603_1608Metric
R304, R305: 1.1k 0.1%; R_0603_1608Metric
R306, R307: 1.0k 0.1%; R_0603_1608Metric
R308, R309: 49.9; R_0603_1608Metric
U301: OPA810IDBV; SOT-23-5
U302: THS4521IDGK; VSSOP-8_3x3mm_P0.65mm

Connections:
+3.3VA: C308.1, U302.3 (V_{S+}), U302.7 (~PD); also elsewhere on the board
+4V5A: C303.1, D301.2 (A), U301.5 (V+); also elsewhere on the board
-4V5A: C304.2, D301.1 (K), U301.2 (V-); also elsewhere on the board
/AFE_B/B_BUF_IN: R303.2, U301.3 (+)
/AFE_B/B_BUF_OUT: R304.1, U301.1, U301.4 (-)
/AFE_B/B_FDA_INN: C306.1, R305.2, R307.1, U302.1 (-)
/AFE_B/B_FDA_INP: C305.1, R304.2, R306.1, U302.8 (+)
/AFE_B/B_IN: C301.1, J301.1 (In), R301.1
/AFE_B/B_OUTN: C305.2, R306.2, R309.1, U302.5
/AFE_B/B_OUTP: C306.2, R307.2, R308.1, U302.4
/AFE_B/B_TAP: C301.2, C302.1, D301.3 (K), R301.2, R302.1, R303.1
AINB_N: C310.1, R309.2; also elsewhere on the board
AINB_P: C309.1, R308.2; also elsewhere on the board
GND: C302.2, C303.2, C304.1, C307.2, C308.2, C309.2, C310.2, J301.2 (Ext), R302.2, R305.1, U302.6 (V_{S-}); also elsewhere on the board
VCMB: C307.1, U302.2 (V_{OCM}); also elsewhere on the board
